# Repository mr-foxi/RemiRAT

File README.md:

# RemiRAT: Versatile Open-Source Wireless Control & Automation Platform
The RemiRAT is a custom PCB that integrates the power of an Arduino Due (SAM3X8EA-AU) with the wireless capabilities of an ESP32-WROOM-32UE-N16 onto a single, compact board. This unified platform condenses complex, multi-board development setups into a streamlined solution, enhancing integration and reliability for advanced control and automation projects.

## Key Features:

Dual Microcontrollers: Combines the SAM3X8EA-AU for high-performance real-time tasks and extensive I/O (including DMA for efficient data handling and RTC support for accurate time-keeping) with the ESP32 for seamless Wi-Fi/Bluetooth connectivity and cloud integration, supporting an external antenna for optimal range.

Robust Industrial Communication: Features dedicated CANBUS (SN65HVD230DR) and MODBUS-RS485 (MAX485CSA+T) transceivers, ensuring reliable data exchange in industrial, automotive, and other demanding environments, complete with proper termination and failsafe biasing for signal integrity.

Diverse Peripherals: Offers comprehensive Digital and Analog I/O, supporting common protocols like UART, SPI, I2C, PWM, and includes a MicroSD card slot for flexible data logging and storage.

Flexible Power Management: Accepts a broad 6.5-32V input via a robust barrel jack or screw terminal, or via USB-C for convenience. It features efficient multi-stage regulation providing stable 5V and 3.3V outputs, backed by integrated fuse protection and USB ESD protection for enhanced durability.

Developer Friendly: Provides multiple options for easy firmware development, including UART, JTAG, and SWD flashing capabilities for both MCUs, along with an ESP32 boot mode DIP switch and clearly labeled breakout headers.

RemiRAT stands as a powerful, robust, and highly integrated solution for tackling complex wireless control and IoT applications with confidence.

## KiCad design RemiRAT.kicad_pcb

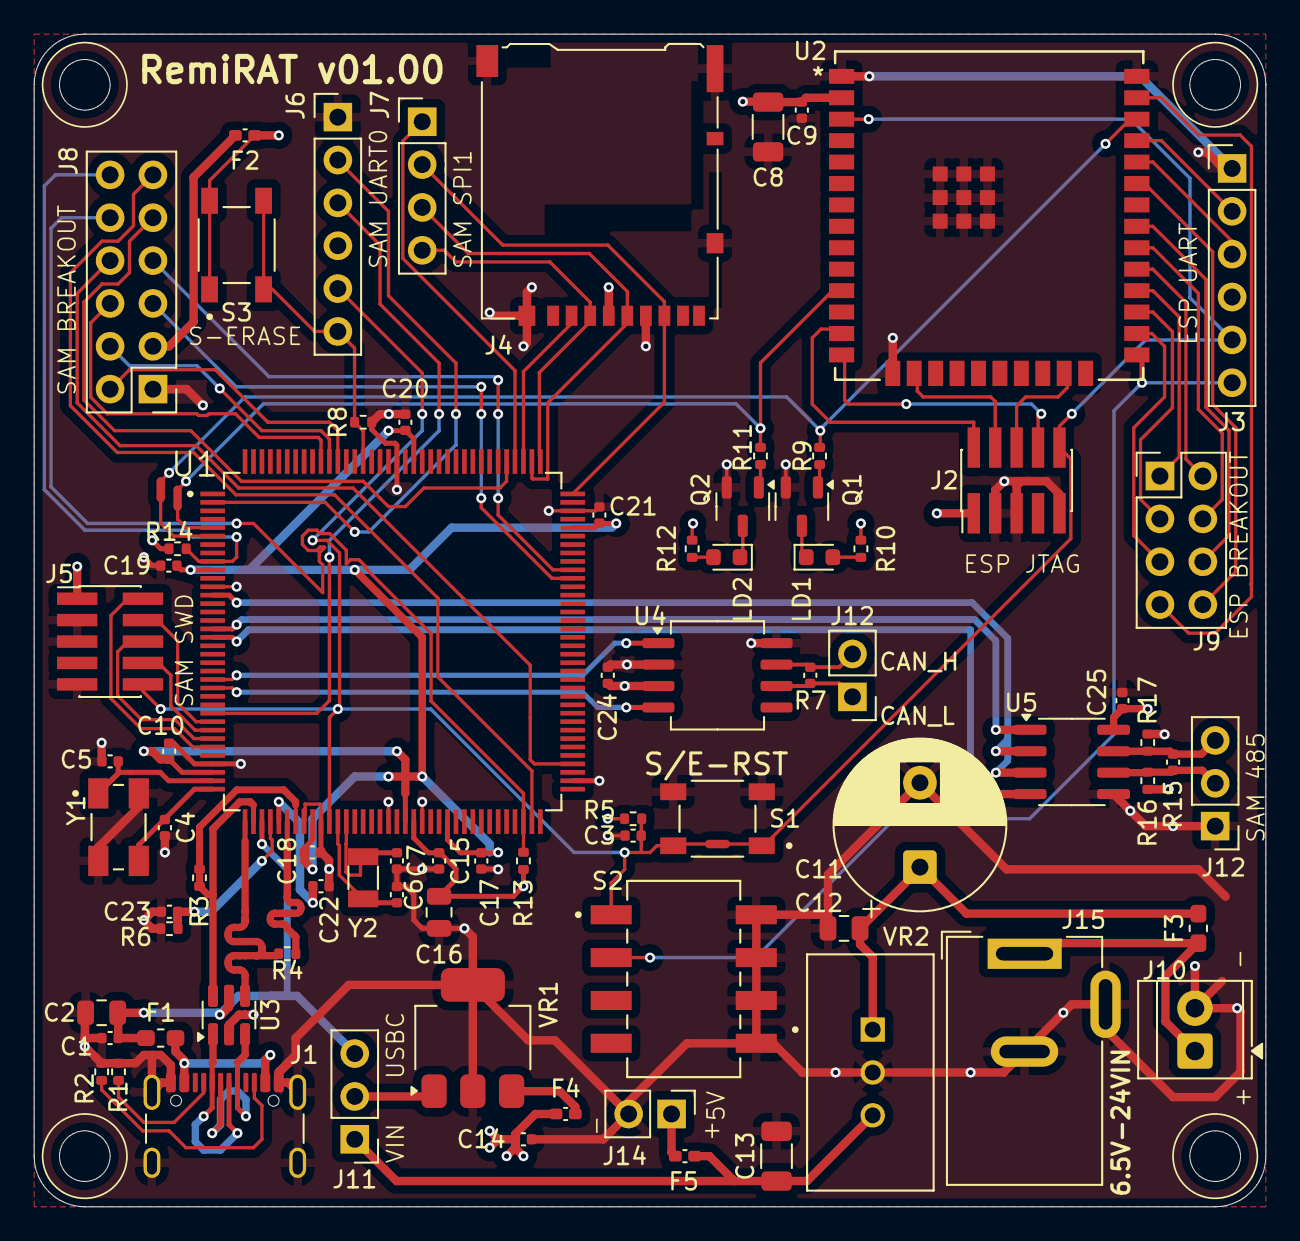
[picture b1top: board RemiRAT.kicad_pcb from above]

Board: 4 copper layers, 73.0 x 69.5 mm, 78 parts (0 on the bottom side), 67 nets.

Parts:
C1, C15, C17, C18, C19, C20, C21, C22, C24, C25: 25V 0.1uF; C_0402_1005Metric
C2, C16: 25V 10uF; C_0805_2012Metric
C3, C9: 0.1uF 25V; C_0402_1005Metric
C4, C5: 18pF 25V; C_0402_1005Metric
C6, C7, C23: 10pF 25V; C_0402_1005Metric
C8: 22uF 25V; C_1206_3216Metric
C10, C14: 1uF 25V; C_0402_1005Metric
C11: 220uF 50V; CP_Radial_D10.0mm_P5.00mm
C12: 1uF 50V; C_0805_2012Metric
C13: 47uF 25V; C_1206_3216Metric
F1: 1.5A 32V SLOWBLOW; Fuse_0603_1608Metric_Pad1.05x0.95mm_HandSolder
F2: 1.5A 32V FASTBLOW; Fuse_0402_1005Metric_Pad0.77x0.64mm_HandSolder
F3: 2A 32V SlowBlow; Fuse_0603_1608Metric_Pad1.05x0.95mm_HandSolder
F4, F5: 1.5A 32V FastBlow; Fuse_0402_1005Metric_Pad0.77x0.64mm_HandSolder
J1: USB_C_Receptacle_GCT_USB4105-xx-A_16P_TopMnt_Horizontal
J2, J5: PinHeader_2x05_P1.27mm_Vertical_SMD
J3, J6: PinHeader_1x06_P2.54mm_Vertical
J4: microSD_HC_Hirose_DM3AT-SF-PEJM5
J7: PinHeader_1x04_P2.54mm_Vertical
J8: PinHeader_2x06_P2.54mm_Vertical
J9: ESP BREAKOUT; PinHeader_2x04_P2.54mm_Vertical
J10: TerminalBlock_TE_282834-2_1x02_P2.54mm_Horizontal
J11: PinHeader_1x03_P2.54mm_Vertical
J12, J14: PinHeader_1x02_P2.54mm_Vertical
J12#2: PinHeader_1x03_P2.54mm_Vertical
J15: BarrelJack_Wuerth_6941xx301002
LD1, LD2: LED_0603_1608Metric
Q1, Q2: SOT-23-3
R1, R2: 5.1K Ohm; R_0402_1005Metric
R3, R4: 39 Ohms; R_0402_1005Metric
R5, R8: 10 kOhms; R_0402_1005Metric
R6: 6.8K Ohm; R_0402_1005Metric
R7, R15: 120 Ohm; C_0402_1005Metric
R9, R11, R13, R14: 4.7K Ohm; R_0402_1005Metric
R10, R12: 200 Ohm; R_0402_1005Metric
R16, R17: 1K Ohm; R_0402_1005Metric
S1, S3: PTS647SN50SMTR2LFS; SW_PTS_647_SN50_SMTR2_LFS
S2: SW_219-4MST
U1: QFP50P2200X2200X145-144N
U2: ESP32-32UE_EXP
U3: SOT-23-6
U4: SOIC-8_5.3x6.2mm_P1.27mm
U5: RS485; SOIC-8_3.9x4.9mm_P1.27mm
VR1: 3.3V-1.5A, Max Input = 20V; SOT-223
VR2: CONV_TSR_2-2450
Y1: 12MHz 13pF 60Ohms; XTAL_405C35B12M00000
Y2: 32.768 kHz 7 pF 70 kOhms; Crystal_SMD_3215-2Pin_3.2x1.5mm

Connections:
3.3V: C8.1, C9.1, C14.1, C15.1, C16.1, C24.1, C25.1, F2.2, F4.1, F4.2, J2.1, J3.4, J4.4, J5.1, J6.4, LD1.2, LD2.2, R5.2, R10.1, R10.2, R12.1, R12.2, R13.2, R14.2, R16.2, S3.1, S3.2, U1.57, U2.2, U4.3, U5.8, VR1.3
3.3VOUT: F2.1, J8.3
A1/PWML5/PC22: J8.2, U1.133
A2/PWML6/PC23: J8.4, U1.134
CANRX0/PA1: U1.24, U4.4
CANTX0/PA0: U1.23, U4.1
CAN_OUT_H: J12.2, R7.2, U4.7
CAN_OUT_L: J12.1, R7.1, U4.6
CC1: J1.A5, R1.1
CC2: J1.B5, R2.1
D14/PC16: J8.5, U1.98
D15/PC17: J8.7, U1.99
EN: J2.10, J3.5, S1.1, U2.3
ERASE/PC0: J6.6, R8.1, S3.3, S3.4, U1.130
ESP32RXD0: J3.3, U2.34
ESP32TXD0: J3.2, U2.35
GND: C1.2, C2.2, C3.2, C4.1, C5.1, C6.2, C7.2, C8.2, C9.2, C10.2, C11.2, C12.2, C13.2, C14.2, C15.2, C16.2, C17.2, C18.2, C19.2, C20.2, C21.2, C22.2, C23.2, C24.2, C25.2, J1.A1, J1.A12, J1.B1, J1.B12, J1.S1, J2.3, J2.5, J2.9, J3.1, J4.6, J4.11, J5.3, J5.5, J5.9, J6.1, J8.1, J10.2, J12#2.1, J14.2, J15.2, J15.3, Q1.2, Q2.2, R1.2, R2.2, R6.2, R8.2, R17.2, S1.3, S1.4, S2.5, S2.6, S2.7, S2.8, U1.12, U1.33, U1.44, U1.46, U1.54, U1.58, U1.74, U1.106, U1.126, U2.1, U2.15, U2.38, U2.39, U2.40, U2.41, U2.42, U2.43, U2.44, U2.45, U2.46, U2.47, U3.2, U4.2, U4.8, U5.5, VR1.2, VR1.4, VR2.2, Y1.2, Y1.4
IO0: J3.6, S2.2, U2.25
IO4: J9.5, U2.26
IO5: J9.2, U2.29
IO16: J9.3, U2.27
IO17: J9.1, U2.28
IO18: J9.4, U2.30
IO19: J9.6, U2.31
IO21: J9.8, U2.33
IO22: LD1.1, Q1.1, Q1.3, R9.1, R9.2, U2.36
IO23: J9.7, U2.37
IO26: LD2.1, Q2.1, Q2.3, R11.1, R11.2, U2.11
MODBUS_A: J12#2.2, R15.1, R16.1, U5.6
MODBUS_B: J12#2.3, R15.2, R17.1, U5.7
NRSTB: C3.1, J5.10, J6.5, R5.1, S1.2, S2.1, U1.47
SAM-JTAG-TCK: J5.4, U1.28
SAM-JTAG-TDI: J5.8, U1.29
SAM-JTAG-TDO: J5.6, U1.30
SAM-JTAG-TMS: J5.2, U1.31
SAM-SPI-MISO: J4.7, J7.2, U1.108
SAM-SPI-MOSI: J4.3, J7.4, U1.109
SAM-SPI-NPCS0: J4.2, U1.111
SAM-SPI-NPCS1: J7.1, U1.112
SAM-SPI-SCK: J4.5, J7.3, U1.110
SAM_A10_PD0_PIN13: U1.13, U5.2, U5.3
SAM_AD5_PA19_PIN71: J8.11, U1.71
SAM_AD6_PB0_PIN113: J8.9, U1.113
SAM_DAC0_PB15_PIN76: J8.8, U1.76
SAM_PWML7_PC24_PIN135: J8.6, U1.135
SAM_USART3_RXD_PD4_PIN17: U1.17, U5.1
SAM_USART3_TXD_PD5_PIN18: U1.18, U5.4
TCK/IO13: J2.4, U2.16
TDI/IO12: J2.8, U2.14
TDO/IO15: J2.6, U2.23
TMS/IO14: J2.2, U2.13
TWCK0/PA18: J8.10, R13.1, U1.70
TWD0/PA17: J8.12, R14.1, U1.9
URXD/PA8: J6.3, U1.27
USBDM: J1.A7, J1.B7, R3.1, R3.2, U1.38, U1.43, U3.1, U3.6
USBDP: J1.A6, J1.B6, R4.1, R4.2, U1.37, U1.42, U3.3, U3.4
UTXD/PA9: J6.2, U1.2
VBG: C23.1, R6.1, U1.40
VBUS: C1.1, C2.1, C13.1, F1.1, F1.2, F5.1, F5.2, J1.A4, J1.A9, J1.B4, J1.B9, J11.1, J11.2, J11.3, J14.1, U1.39, U3.5, VR1.1, VR2.3
VDDCORE: C17.1, C18.1, C19.1, C20.1, C21.1, U1.10, U1.45, U1.61, U1.104, U1.124
VDDPLL: C10.1, U1.34
VDDUTMI: C22.1, U1.41
VIN: C11.1, C12.1, F3.1, F3.2, J10.1, J15.1, VR2.1
XIN: C4.2, U1.36, Y1.3
XIN32: C6.1, U1.48, Y2.2
XOUT: C5.2, U1.35, Y1.1
XOUT32: C7.1, U1.49, Y2.1

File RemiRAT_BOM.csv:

Id,Designator,Footprint,Quantity,Designation,Manufacturer,Manufacturer Part Number,Notes,,
1,J9,PinHeader_2x04_P2.54mm_Vertical,1,Header 2x04 Pin 2.54mm Vertical,Samtec Inc.,TSW-104-07-F-D,Generic Header,,
2,"R11,R9,R13",R_0402_1005Metric,2,Resistor 4.7k Ohm 1% 0402,Yageo,RC0402FR-074K7L,"Pull-up/down, specific for SAM or ESP",,
3,"J3,J6",PinHeader_1x06_P2.54mm_Vertical,2,Header 1x06 Pin 2.54mm Vertical,Würth Elektronik,61300611121,"e.g., Serial Flashing Headers",,
4,"C23,C7,C6",C_0402_1005Metric,3,Capacitor 10pF 25V 0402,KYOCERA AVX,KGM05ACG1E100KH,Crystal Load Capacitors,,
5,"S3,S1",SW_PTS_647_SN50_SMTR2_LFS,2,Tactile Switch SPST-NO SMD,C&K Components,PTS647SN50SMTR2LFS,Reset/Erase Buttons,,
6,"Q2,Q1",SOT-23-3,2,N-Channel MOSFET SOT-23,Anbon,BC847B,RX/TX LED Transistor,,
7,"R4,R3",R_0402_1005Metric,2,Resistor 39 Ohm 1% 0402,Stackpole Electronics Inc,RMCF0402JT39R0,USB D+/D- Termination,,
8,"R5,R8",R_0402_1005Metric,2,Resistor 10k Ohm 1% 0402,Yageo,RC0402FR-0710KL,Pull-up/down for control lines,,
9,C8,C_1206_3216Metric,1,Capacitor 22uF 25V X5R 1206,Samsung Electro-Mechanics,CL31A226KAHNNNE,Bulk Decoupling/Output Cap for ESP32,,
10,U1,QFP50P2200X2200X145-144N,1,ATSAM3X8AE-AU MCU,Microchip,ATSAM3X8EA-AU,Main Microcontroller,,
12,"LD1,LD2",LED_0603_1608Metric,2,LED Green 0603,Kingbright,APT1608CGCK,RX/TX ESP/SAM LEDs,,
13,J4,microSD_HC_Hirose_DM3AT-SF-PEJM5,1,MicroSD Card Connector,Hirose,DM3AT-SF-PEJM5,MicroSD Slot,,
14,VR1,SOT-223,1,LDO Regulator 3.3V 1.5A,STMicroelectronics,TL1963A-33DCYR,3.3V Power Supply,,
15,C10,C_0402_1005Metric,1,Capacitor 1uF 25V X5R 0402,Samsung Electro-Mechanics,CL05A105KA5NQNC,PinHeader_1x06_P2.54mm_Vertical,2,PinHeader_1x06_P2.54mm_Vertical
16,Y1,XTAL_405C35B12M00000,1,Crystal 12MHz 13pF 4-SMD,CTS-Frequency Controls,405C35B12M00000,Main SAM MCU Crystal,,
17,"R1,R2",R_0402_1005Metric,2,Resistor 5.1k Ohm 1% 0402,Yageo,RC0402FR-075K1L,Could be USB pull-ups or other,,
18,J7,PinHeader_1x04_P2.54mm_Vertical,1,Header 1x04 Pin 2.54mm Vertical,Würth Elektronik,61300411121,"e.g., Test Points, I2C",,
19,"R10,R12",R_0402_1005Metric,2,Resistor 200 Ohm 1% 0402,Delta Electronics/Cyntec,PFR05S-201-FNH,LED Current Limiting,,
20,"C2,C16",C_0805_2012Metric,1,Capacitor 10uF 25V X5R 0805,Samsung Electro-Mechanics,CL21A106KAYNNNE,Input/Output Decoupling,,
21,J1,USB_C_Receptacle_GCT_USB4105-xx-A_16P_TopMnt_Horizontal,1,USB-C Receptacle Horizontal,GCT,USB4105-GF-A,USB Connector,,
22,"J2,J5",PinHeader_2x05_P1.27mm_Vertical_SMD,2,Header 2x05 Pin 1.27mm Vert SMD,CNC Tech,3220-10-0300-00 ,"e.g., SWD/JTAG Headers",,
23,S2,SW_219-4MST,1,DIP Switch 4-Pos SPST,CTS Electrocomponents,219-4MST,"e.g., ESP32 Boot Mode Select",,
24,J8,PinHeader_2x06_P2.54mm_Vertical,1,Header 2x06 Pin 2.54mm Vertical,TE Connectivity AMP Connectors,87227-6,"e.g., Generic Expansion Header",,
25,U2,ESP32-32UE_EXP,1,ESP32-WROOM-32UE Module,Espressif Systems,ESP32-WROOM-32UE-N16,Wi-Fi/BT Module,,
26,"C4,C5",C_0402_1005Metric,2,Capacitor 18pF 25V C0G 0402,KYOCERA AVX,KGM05ACG1E180FH,Crystal Load Capacitor,,
28,"C24,C22,C21,C20,C19,C18,C17,C15,C9,C3,C1",C_0402_1005Metric,10,Capacitor 0.1uF 25V X7R 0402,Samsung Electro-Mechanics,CL05B104KA5NNNC,Local Decoupling,,
29,"F1,F2",Fuse_0402_1005Metric_Pad0.77x0.64mm_HandSolder,2,Fuse 1.5A 32V 0402,Littelfuse,043501.5KRHF,Overcurrent Protection,,
30,Y2,Crystal_SMD_3215-2Pin_3.2x1.5mm,1,Crystal 32.768kHz 7pF 3.2x1.5mm,Seiko Instruments,SC32S-7PF20PPM,RTC Crystal for SAM,,
31,U3,SOT-23-6,1,Voltage Supervisor SOT-23-6,STMicroelectronics,USBLC6-2,"Example, specify part type (e.g. voltage supervisor, op-amp, logic IC)",,
32,F3,Fuse_0603_1608Metric_Pad1.05x0.95mm_HandSolder,1,2A 32V SlowBlow,Bourns Inc.,SF-0603SP200-2,Wire Input Power Fuse,,
33,VR2,CONV_TSR_2-2450,1,Wire Power Input Voltage Regulator,Traco Power,TSR 2-2450,,,
34,C12,C_0805_2012Metric,1,1uF 50V,Samsung Electro-Mechanics,CL21B105KBFNNNE,,,
35,J10,TerminalBlock_TE_282834-2_1x02_P2.54mm_Horizontal,1,,TE Connectivity AMP Connectors,1546215-2,,,
36,J11,PinHeader_1x03_P2.54mm_Vertical,1,PinHeader_1x03_P2.54mm_Vertical,Würth Elektronik,61300311121,,,
37,C13,C_1206_3216Metric,1,47uF 25V,TDK Corporation,C3216X5R1E476M160AC,,,
38,"C10,C14",C_0402_1005Metric,2,1uF 25V,Samsung Electro-Mechanics,CL05A105KA5NQNC,Local Decoupling,,
39,R6,R_0402_1005Metric,1,Resistor 6.8K Ohm 1% 0402,TE Connectivity Passive Product,CRGCQ0402F6K8,,,
40,U4,SOIC-8_5.3x6.2mm_P1.27mm,1,1/1 IC Transceiver Half CANbus 8-SOIC,Texas Instruments,SN65HVD230DR,,,
41,J11,PinHeader_1x02_P2.54mm_Vertical,,Header 1x02 Pin 2.54mm Vertical,Würth Elektronik,61300211121,CANBUS Breakout,,
42,R7,R_0402_1005Metric,,Resistor 120 Ohm 1% 0402,Vishay Dale,CRCW0402120RFKEDC,CABUS Noise Resistor,,

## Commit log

2025-07-13 Rename Screenshot_20250713_211909.png to PCB_TOP.png
2025-07-13 Rename Screenshot_20250713_211952.png to PCB_BOTTOM.png
2025-07-13 Rename Screenshot_20250713_212033.png to Cu_TOP.png
2025-07-13 Rename Screenshot_20250713_212114.png to SilkScreen_TOP.png
2025-07-13 Rename Screenshot_20250713_212139.png to Schem.png
2025-07-13 Rename Screenshot_20250713_213235.png to Schem_01.png
2025-07-13 Rename Screenshot_20250713_213324.png to Schem_02.png
2025-07-13 Rename Screenshot_20250713_213342.png to Schem_03.png
2025-07-13 Rename Screenshot_20250713_213414.png to Schem_04.png
